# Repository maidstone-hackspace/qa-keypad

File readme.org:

#+TITLE: Wemos QA keypad

* Device install

To setup a new device you can use the arduino software, you will need a plugin to upload the files in the =data= folder to your wemos device.

** Deploy requirements
https://github.com/esp8266/Arduino.git
https://github.com/esp8266/arduino-esp8266fs-plugin/releases/tag/0.4.0

** Build Requirements
You will also need various 3rd party libaries.
keypad.h 3.1.1 by Mark Stanley, Alexander Brevig https://wiring.uniandes.edu.co/source/trunk/wiring/

LiquidCrystal I2C by frank de Bradander https://github.com/johnrickman/LiquidCrystal_I2C

ESPAsyncWebServer https://github.com/me-no-dev/ESPAsyncWebServer/archive/master.zip

ESPAsyncTCP https://github.com/me-no-dev/ESPAsyncTCP

Extract and copy to arduino libries folder

* Device Setup

When switching on the device for the first time it will launch in access point mode to allow you to setup the device, connect to =weeeecfg= from a phone and enter password =weeeecfg= to setup the device. If the device can not connect to a local network it will relaunch the setup interface.

subsequent usage of the device will reuse the same settings as long as the device can connect.

The interfacing is using a simple web interface generated from this repository.

https://gitlab.com/olymk2/weecfg

#+RESULTS:
: None

* API example
** Keypad startup endpoint
#+BEGIN_SRC http :pretty :exports both
POST http://ng.snapwire-portal.co.uk/api/Startup
Content-Type: application/json

{"ControllerId": "DID1"}
#+END_SRC

#+RESULTS:
: {
:   "ControllerId": "DID1",
:   "AssignedName": "Bob"
: }

** Poll to determine when ready for next answer
#+BEGIN_SRC http :pretty :exports both
POST http://ng.snapwire-portal.co.uk/api/Poll
Content-Type: application/json

{}
#+END_SRC

#+RESULTS:
: {
:   "Timestamp": 132149528062145583,
:   "ReadyToAcceptAnswers": true
: }

** Example sending answer to api.
#+BEGIN_SRC http :pretty :exports both
POST http://ng.snapwire-portal.co.uk/api/SubmitAnswer
Content-Type: application/json

{"ControllerId": "sample string 1", "Answer": "A"}
#+END_SRC

#+RESULTS:
: {
:   "ConfirmReceived": true
: }

http://ng.snapwire-portal.co.uk/api/SubmitAnswer

* Later
** TODO gzip the html

The wemos is by no means fast so gzip so there is less data to send.
** TODO http error message on api failure.

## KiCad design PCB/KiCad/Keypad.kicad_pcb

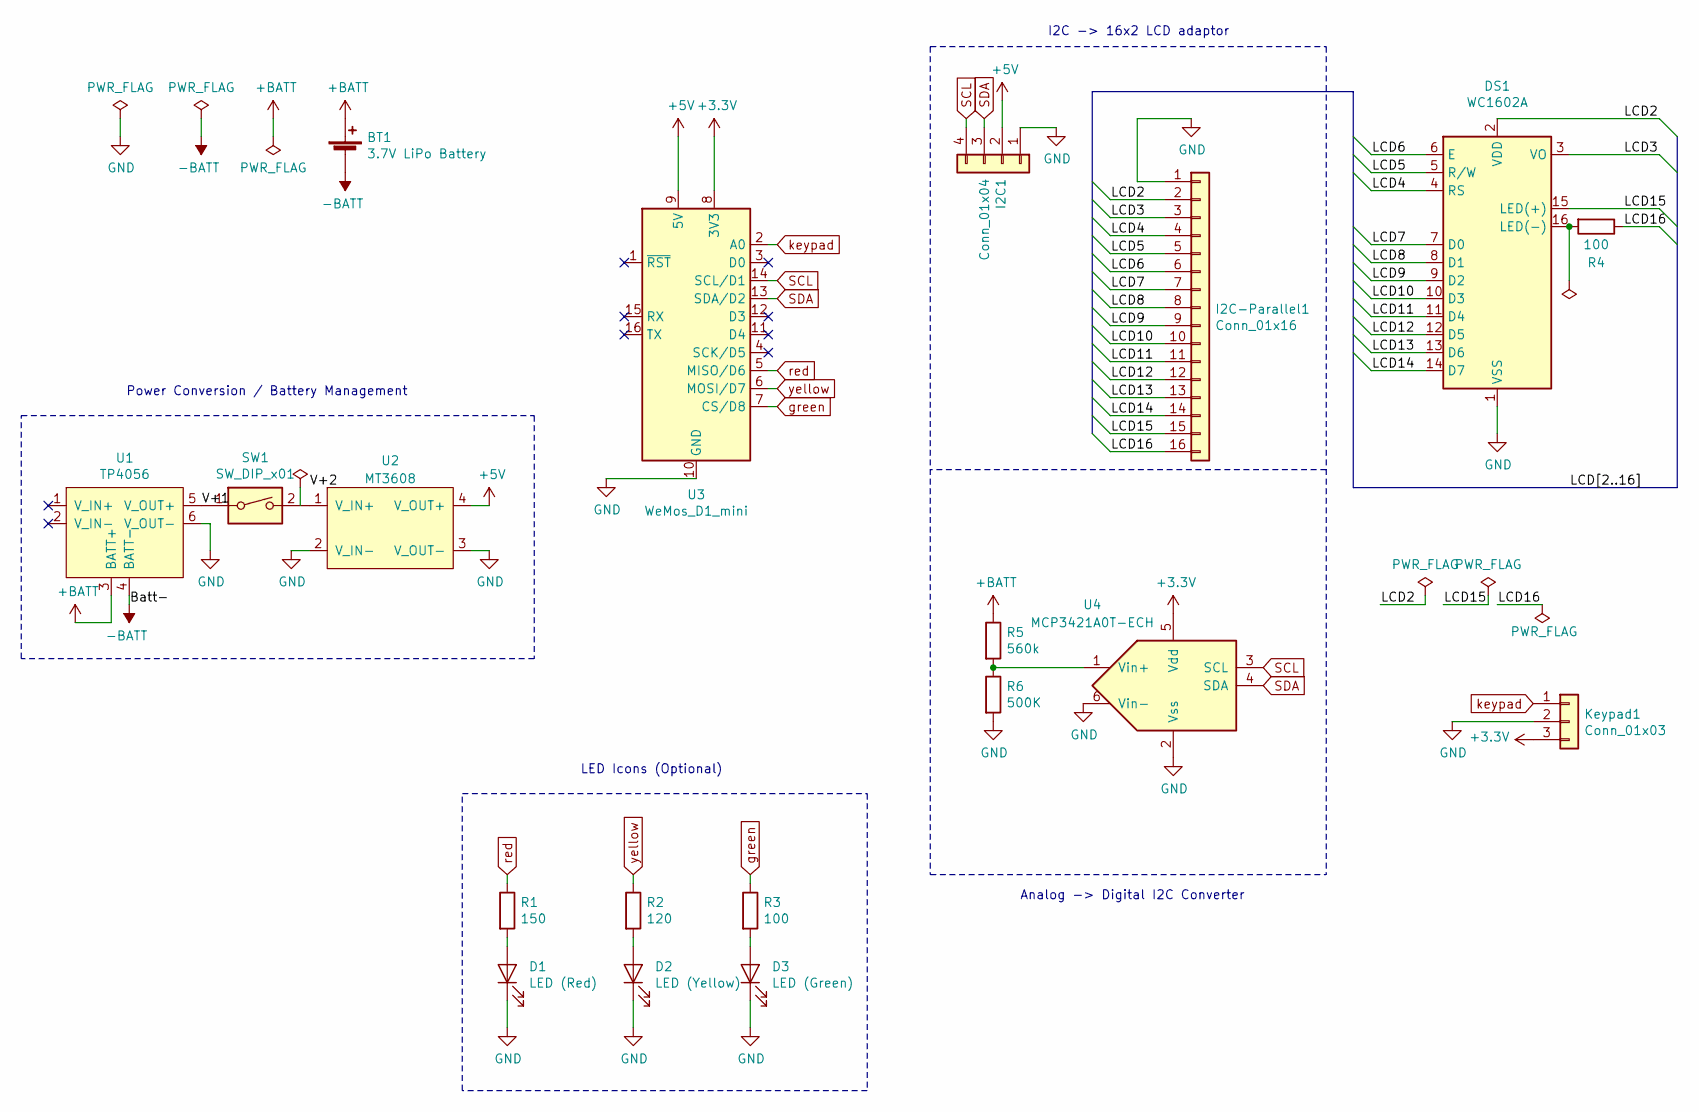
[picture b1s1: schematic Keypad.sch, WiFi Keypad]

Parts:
BT1: 3.7V LiPo Battery; JST_XH_B2B-XH-A_1x02_P2.50mm_Vertical
D1: LED (Red); LED_D3.0mm
D2: LED (Yellow); LED_D3.0mm
D3: LED (Green); LED_D3.0mm
DS1: WC1602A
I2C1: Conn_01x04; PinHeader_1x04_P2.54mm_Vertical
I2C-Parallel1: Conn_01x16; PinHeader_1x16_P2.54mm_Vertical
Keypad1: Conn_01x03; PinHeader_1x03_P2.54mm_Vertical
R1: 150; R_Axial_DIN0207_L6.3mm_D2.5mm_P10.16mm_Horizontal
R2: 120; R_Axial_DIN0207_L6.3mm_D2.5mm_P10.16mm_Horizontal
R3, R4: 100; R_Axial_DIN0207_L6.3mm_D2.5mm_P10.16mm_Horizontal
R5: 560k; R_Axial_DIN0207_L6.3mm_D2.5mm_P10.16mm_Horizontal
R6: 500K; R_Axial_DIN0207_L6.3mm_D2.5mm_P10.16mm_Horizontal
SW1: SW_DIP_x01; Mini_Latching_Torch_Switch
U1: TP4056; 4056E_LiIon_loader_SMT
U2: MT3608; MT3608_module_SMT
U3: WeMos_D1_mini; WEMOS_D1_mini_light
U4: MCP3421A0T-ECH; SOT-23-6_Handsoldering

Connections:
+3V3: Keypad1.3, U3.8 (3V3), U4.5 (Vdd)
+5V: I2C1.2, U2.4 (V_OUT+), U3.9 (5V); also elsewhere on the board
+BATT: BT1.1 (+), R5.1, U1.3 (BATT+)
-BATT: BT1.2 (-), U1.4 (BATT-)
/LCD2: DS1.2 (VDD), I2C-Parallel1.2
/LCD3: DS1.3 (VO), I2C-Parallel1.3
/LCD4: DS1.4 (RS), I2C-Parallel1.4
/LCD5: DS1.5 (R/W), I2C-Parallel1.5
/LCD6: DS1.6 (E), I2C-Parallel1.6
/LCD7: DS1.7 (D0), I2C-Parallel1.7
/LCD8: DS1.8 (D1), I2C-Parallel1.8
/LCD9: DS1.9 (D2), I2C-Parallel1.9
/LCD10: DS1.10 (D3), I2C-Parallel1.10
/LCD11: DS1.11 (D4), I2C-Parallel1.11
/LCD12: DS1.12 (D5), I2C-Parallel1.12
/LCD13: DS1.13 (D6), I2C-Parallel1.13
/LCD14: DS1.14 (D7), I2C-Parallel1.14
/LCD15: DS1.15 (LED(+)), I2C-Parallel1.15
/LCD16: I2C-Parallel1.16, R4.1
/V+1: SW1.1, U1.5 (V_OUT+)
GND: D1.1 (K), D2.1 (K), D3.1 (K), DS1.1 (VSS), I2C1.1, I2C-Parallel1.1, Keypad1.2, R6.2, U1.6 (V_OUT-), U2.2 (V_IN-), U2.3 (V_OUT-), U3.10 (GND), U4.2 (Vss), U4.6 (Vin-); also elsewhere on the board
unnamed: D1.2 (A), R1.2
unnamed: D2.2 (A), R2.2
unnamed: D3.2 (A), R3.2
unnamed: DS1.16 (LED(-)), R4.2
unnamed: R5.2, R6.1, U4.1 (Vin+)
unnamed: SW1.2, U2.1 (V_IN+)
SCL: I2C1.4, U3.14 (SCL/D1), U4.3 (SCL)
SDA: I2C1.3, U3.13 (SDA/D2), U4.4 (SDA)
green: R3.1, U3.7 (CS/D8)
keypad: Keypad1.1, U3.2 (A0)
red: R1.1, U3.5 (MISO/D6)
yellow: R2.1, U3.6 (MOSI/D7)

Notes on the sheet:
I2C -> 16x2 LCD adaptor
Analog -> Digital I2C Converter
LED Icons (Optional)
Power Conversion / Battery Management

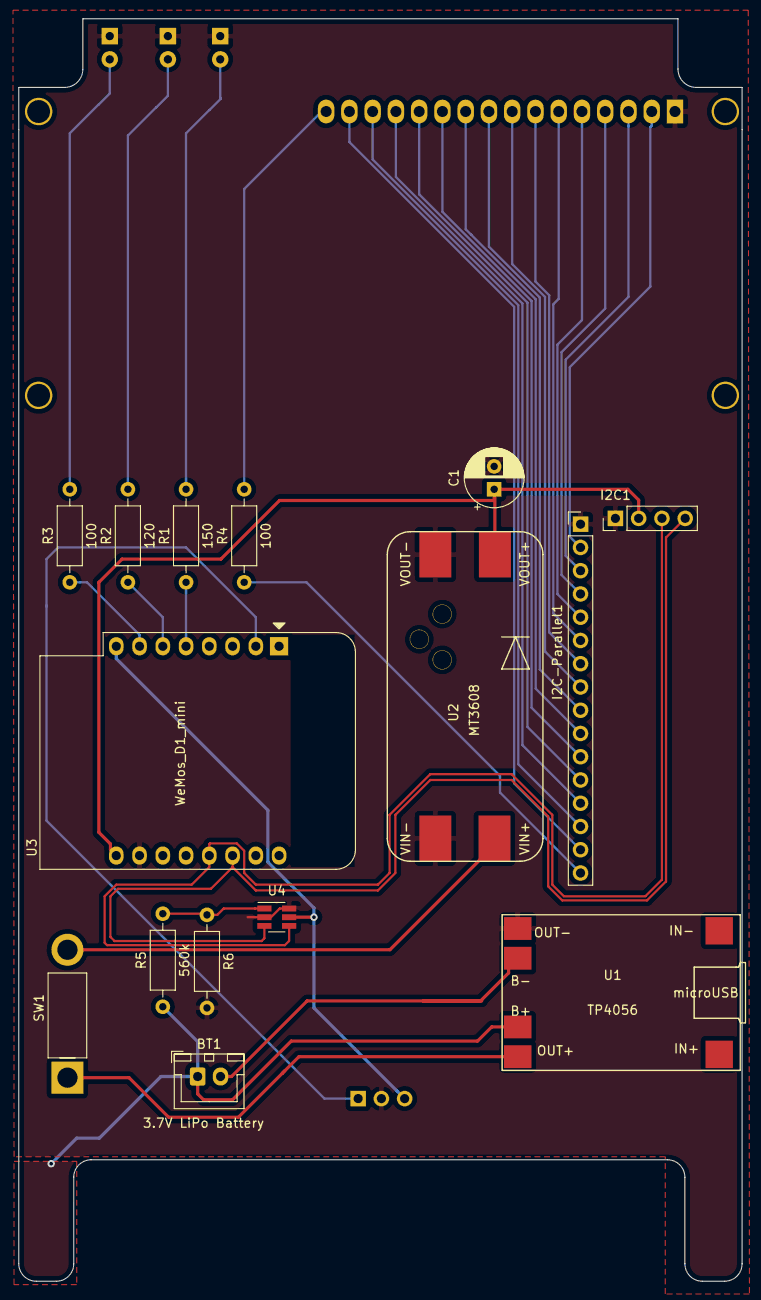
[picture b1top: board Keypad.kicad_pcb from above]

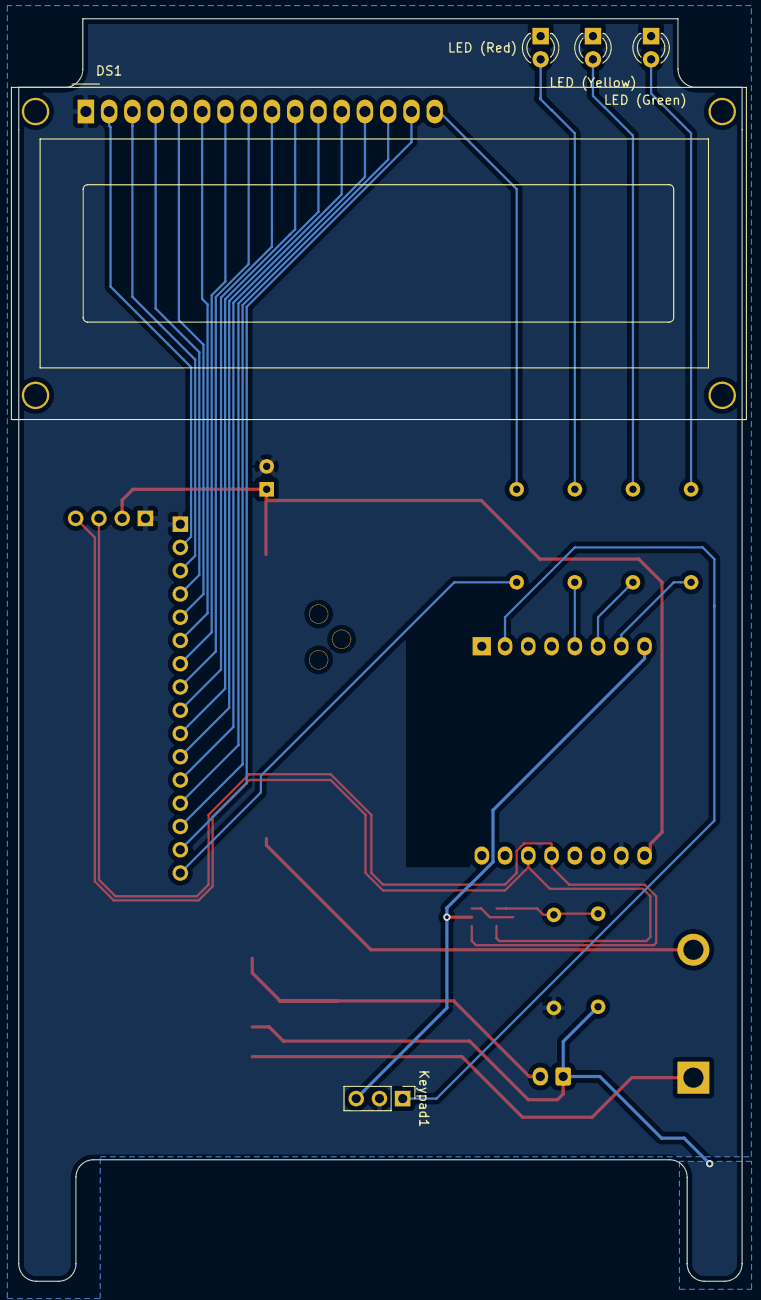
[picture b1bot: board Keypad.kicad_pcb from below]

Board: 2 copper layers, 79.0 x 137.9 mm, 20 parts (5 on the bottom side), 33 nets.

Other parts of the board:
C1: 100u; CP_Radial_D6.3mm_P2.50mm

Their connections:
+5V: C1.1; also elsewhere on the board
GND: C1.2; also elsewhere on the board

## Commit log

2019-09-19 Initial code to setup the device on a local network.
2019-09-19 Remove debug code from diagnosing an exception.
2019-09-23 Add in basic lcd code.
2019-10-07 Basic lcd code, and sample json request code.
2019-10-07 Remove compression extension, not compressed yet.
2019-10-07 Remove wificlient, break out config for api.
2019-10-07 First working request to json api.
2019-10-07 Formatted example results.
2019-10-09 Further work on api, returned values in startup and dummy code for other endpoints.
2019-10-14 Current code, now displays user name on screen.
2019-10-16 Improved lcd support.
2019-10-17 Added rev 1 PCB files
2019-10-28 Add compressed assets.
2020-01-15 Add code for new keypad, code maps to chars small bug needs fixing with linking.
2020-01-20 Fix linking issue, and rename from wemos to avoid conflicts.
2020-02-01 Analog Keypad
    Revision to use analog output keypad.
2020-02-05 kicad files updated.
2020-02-06 parts list
2020-03-02 Add esp8266 link.
2020-03-02 Add missing libraries.
2020-04-07 adjustments
    LCD moved 2mm in. Wemos rotated 180. 100uF cap added.
